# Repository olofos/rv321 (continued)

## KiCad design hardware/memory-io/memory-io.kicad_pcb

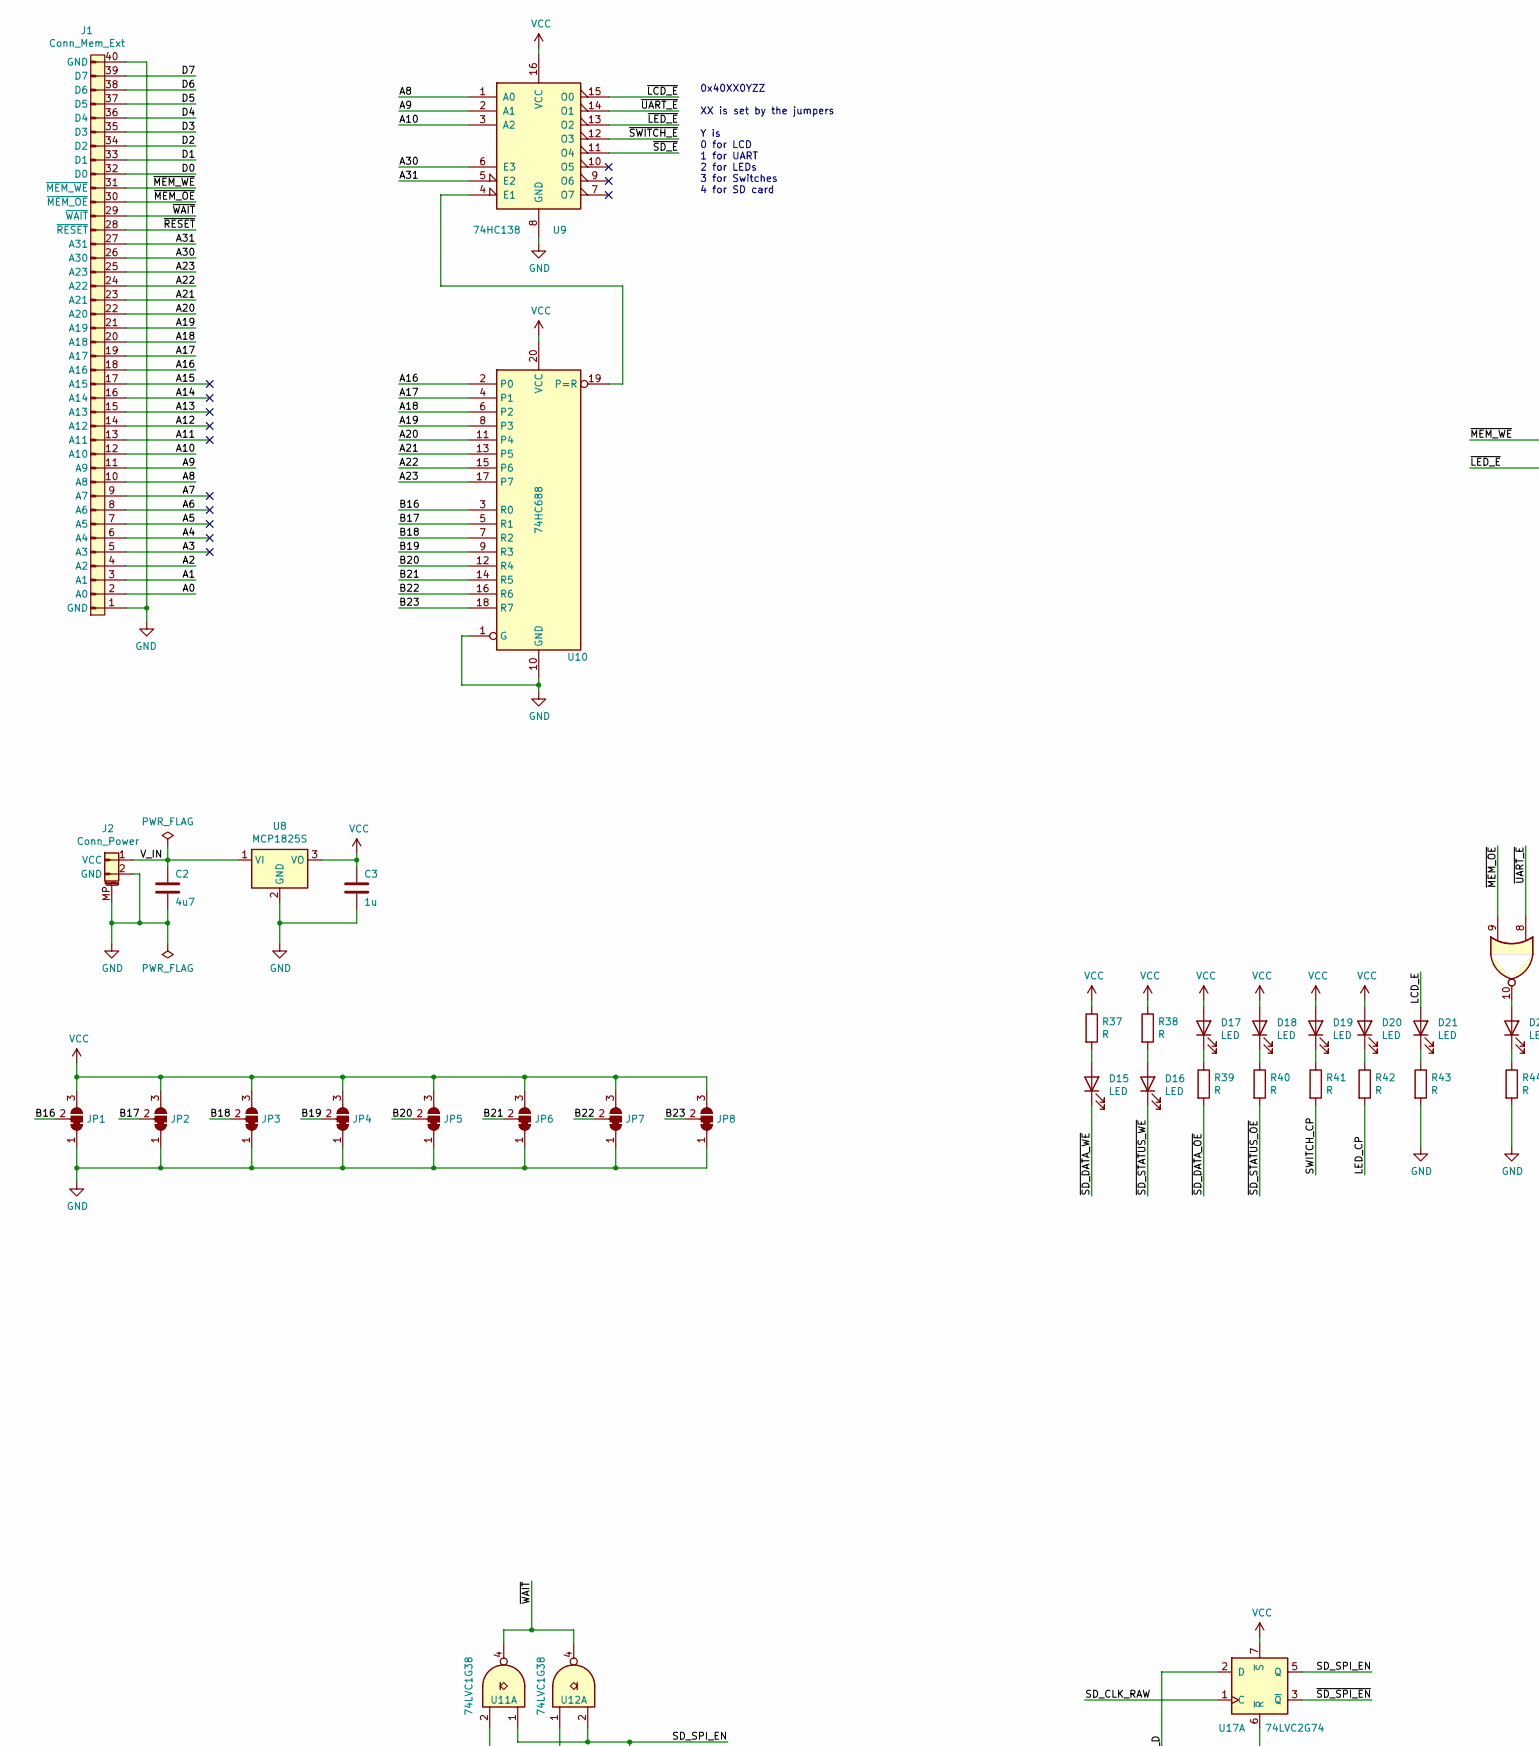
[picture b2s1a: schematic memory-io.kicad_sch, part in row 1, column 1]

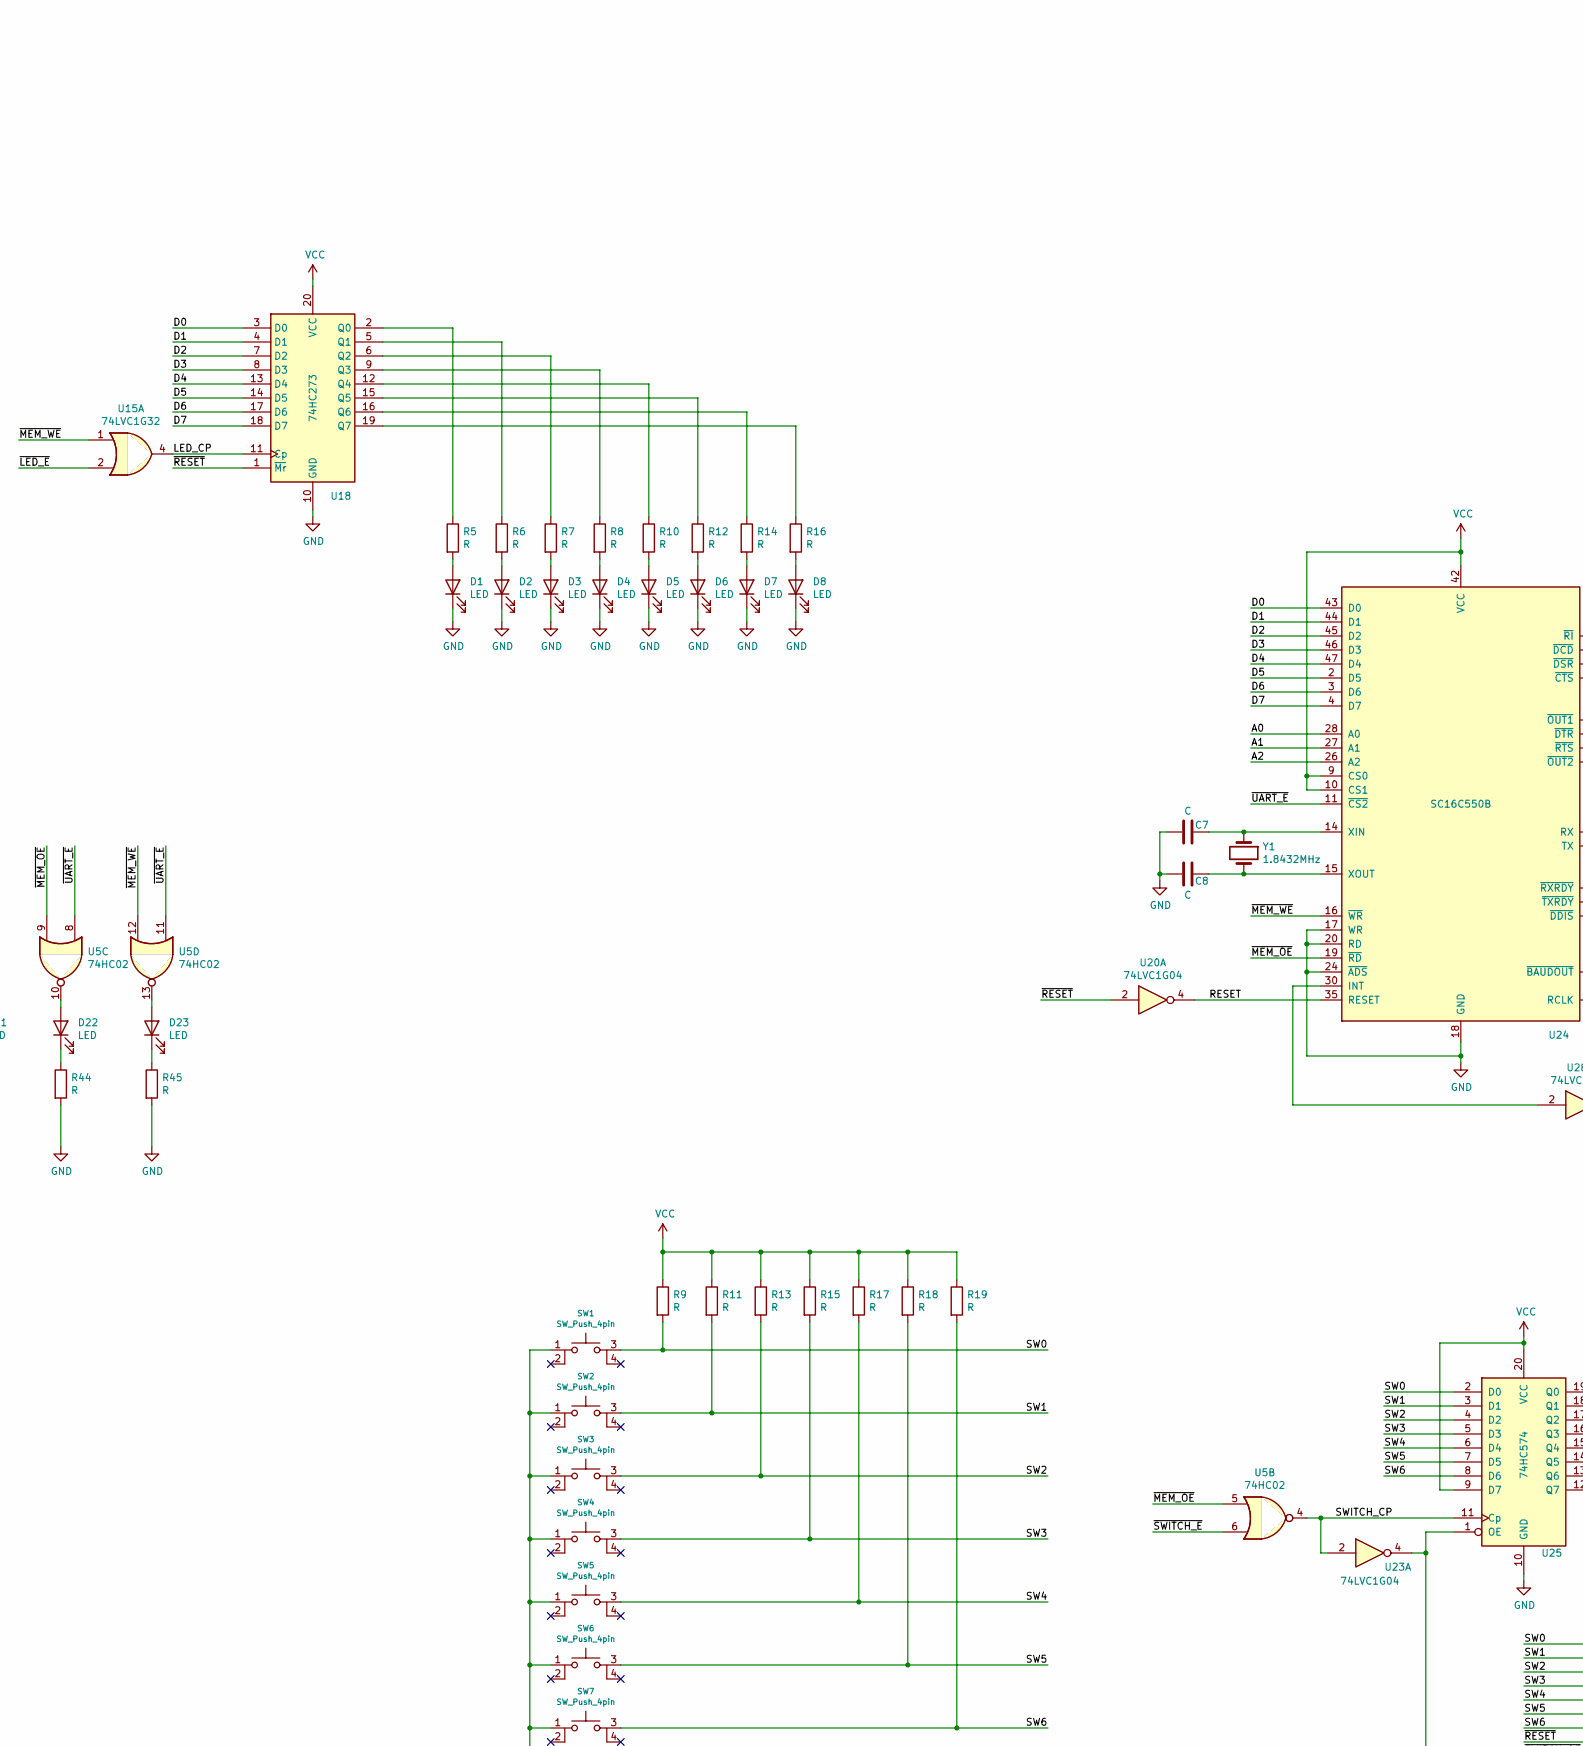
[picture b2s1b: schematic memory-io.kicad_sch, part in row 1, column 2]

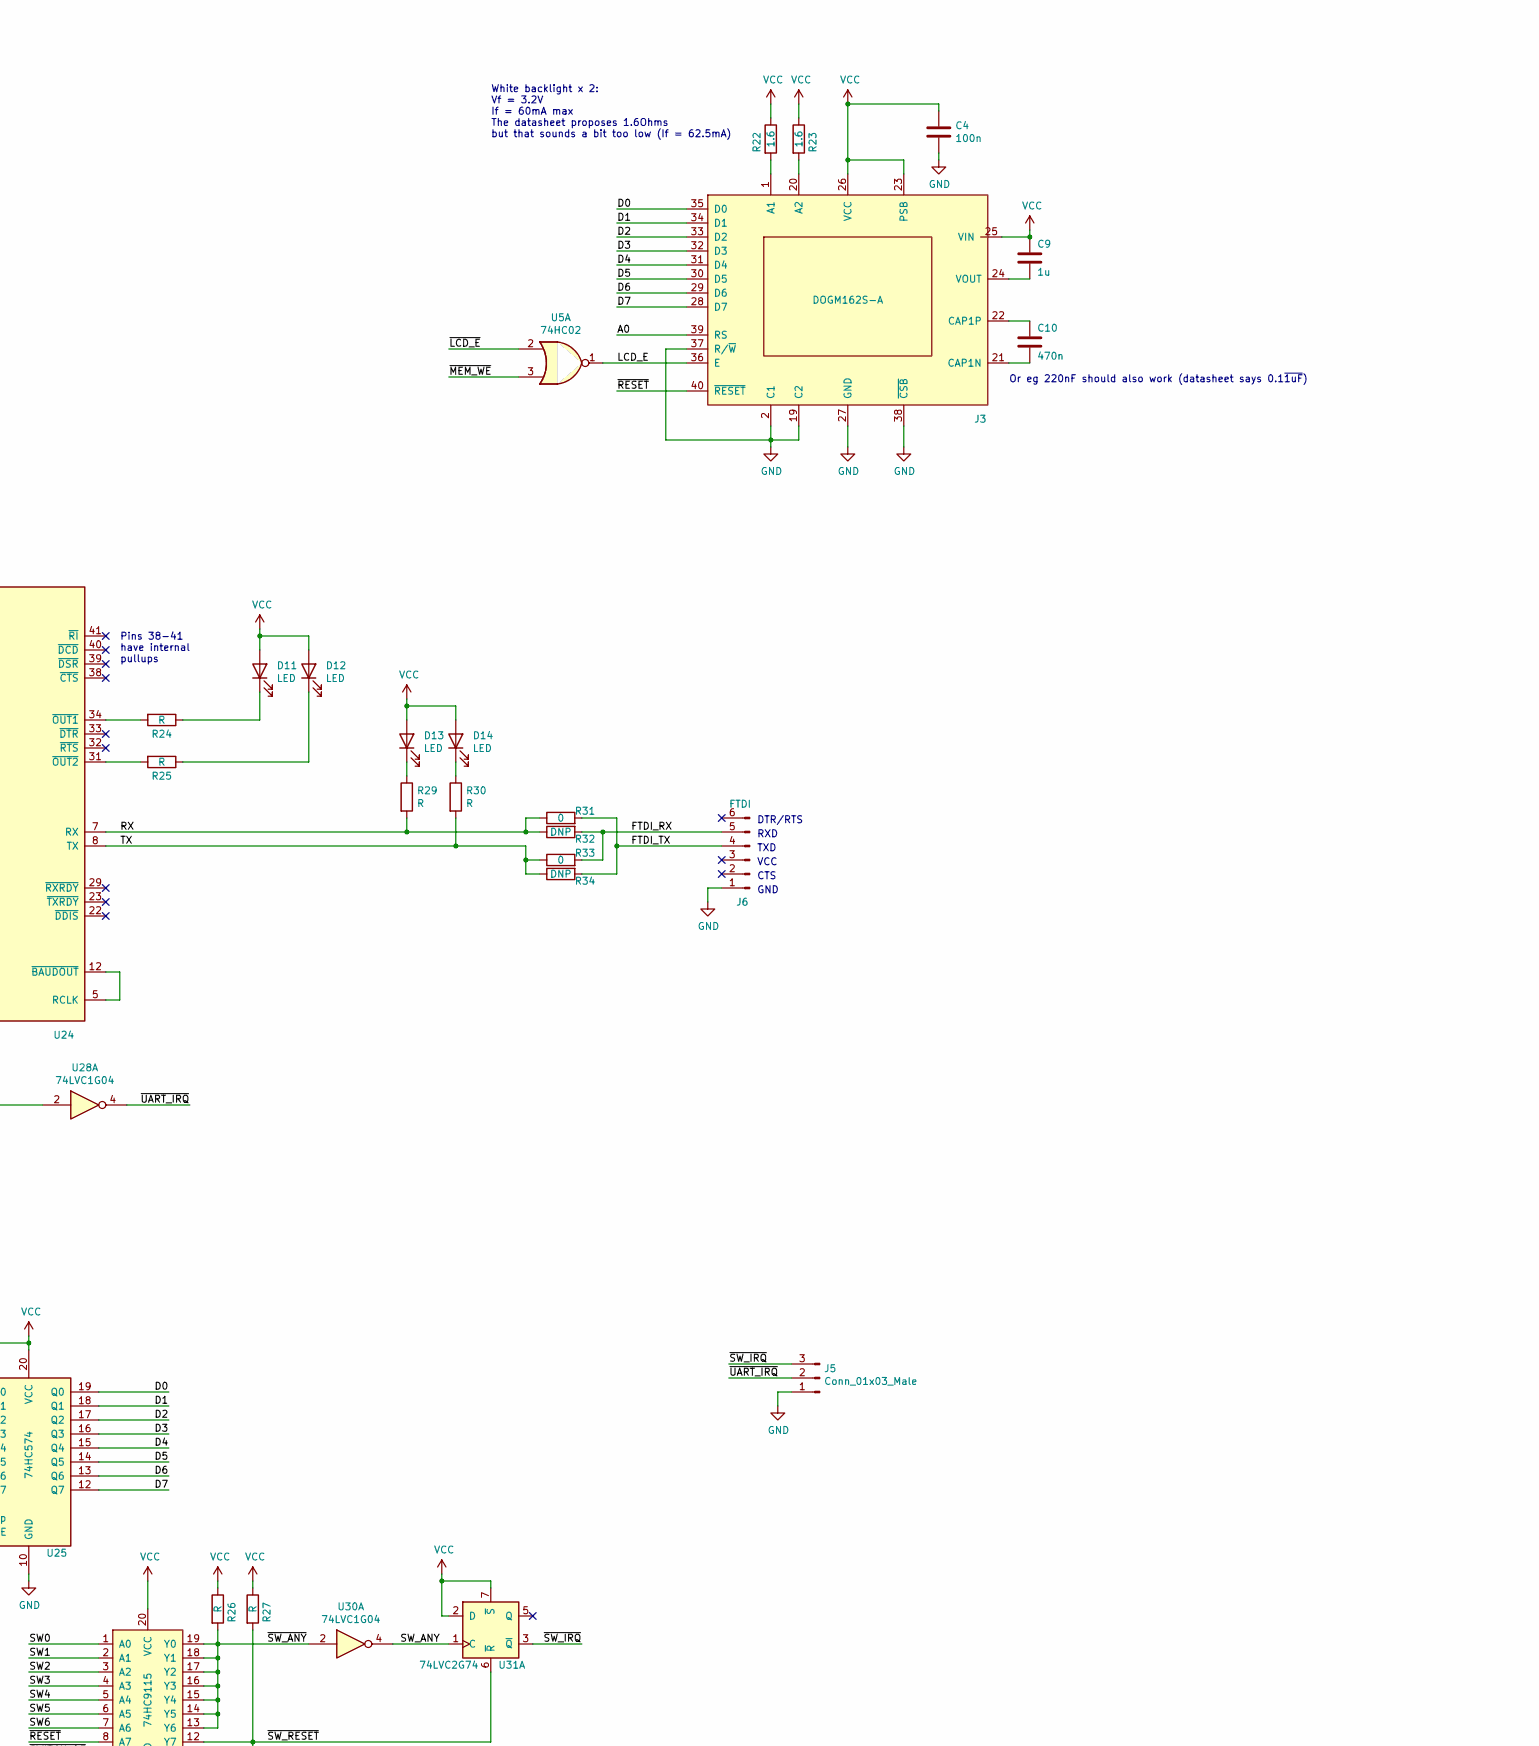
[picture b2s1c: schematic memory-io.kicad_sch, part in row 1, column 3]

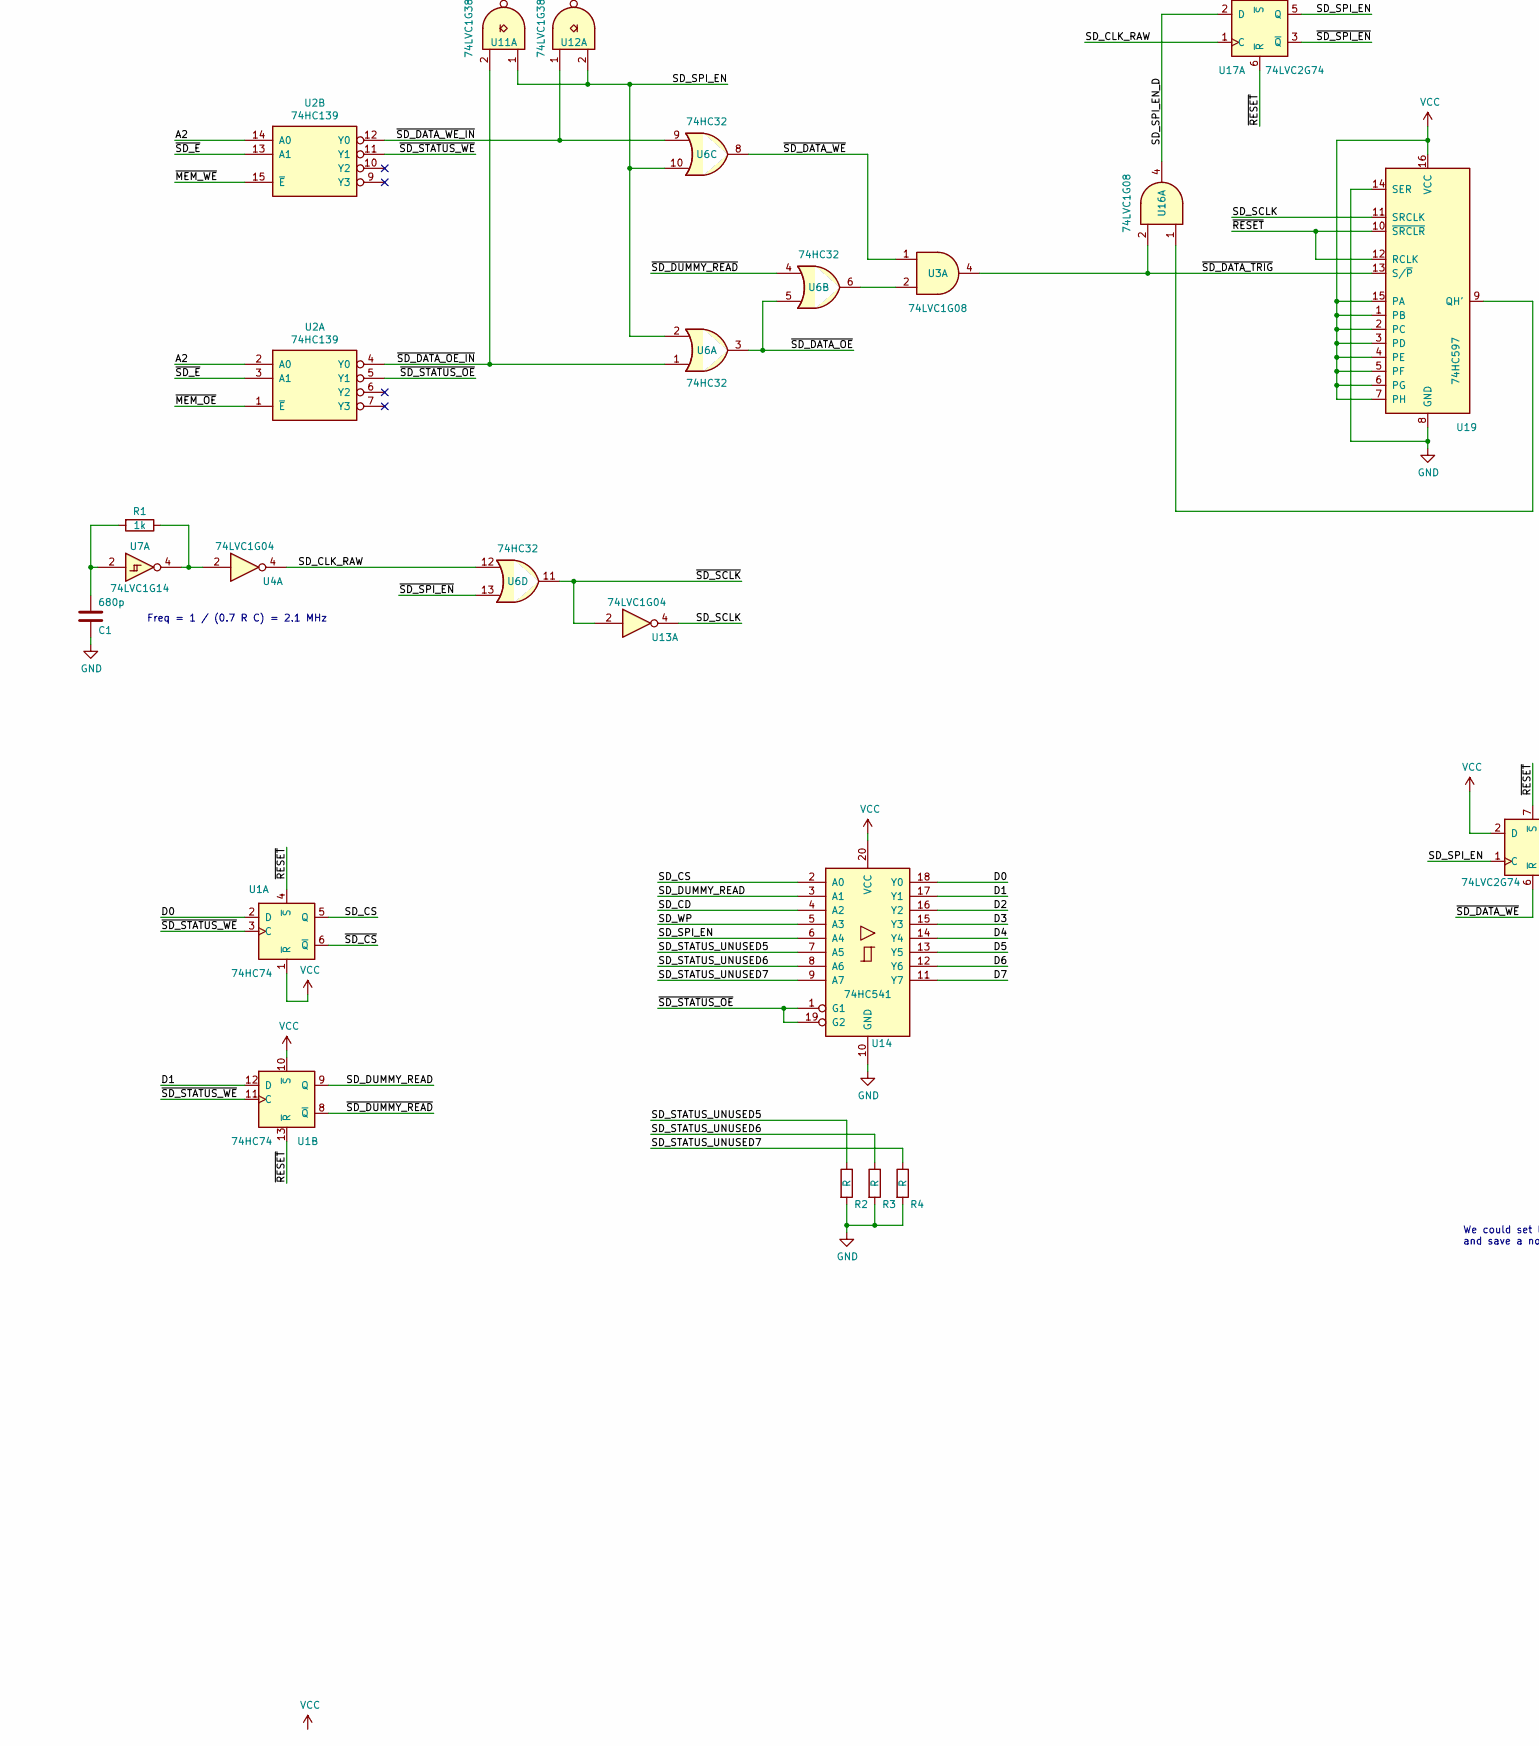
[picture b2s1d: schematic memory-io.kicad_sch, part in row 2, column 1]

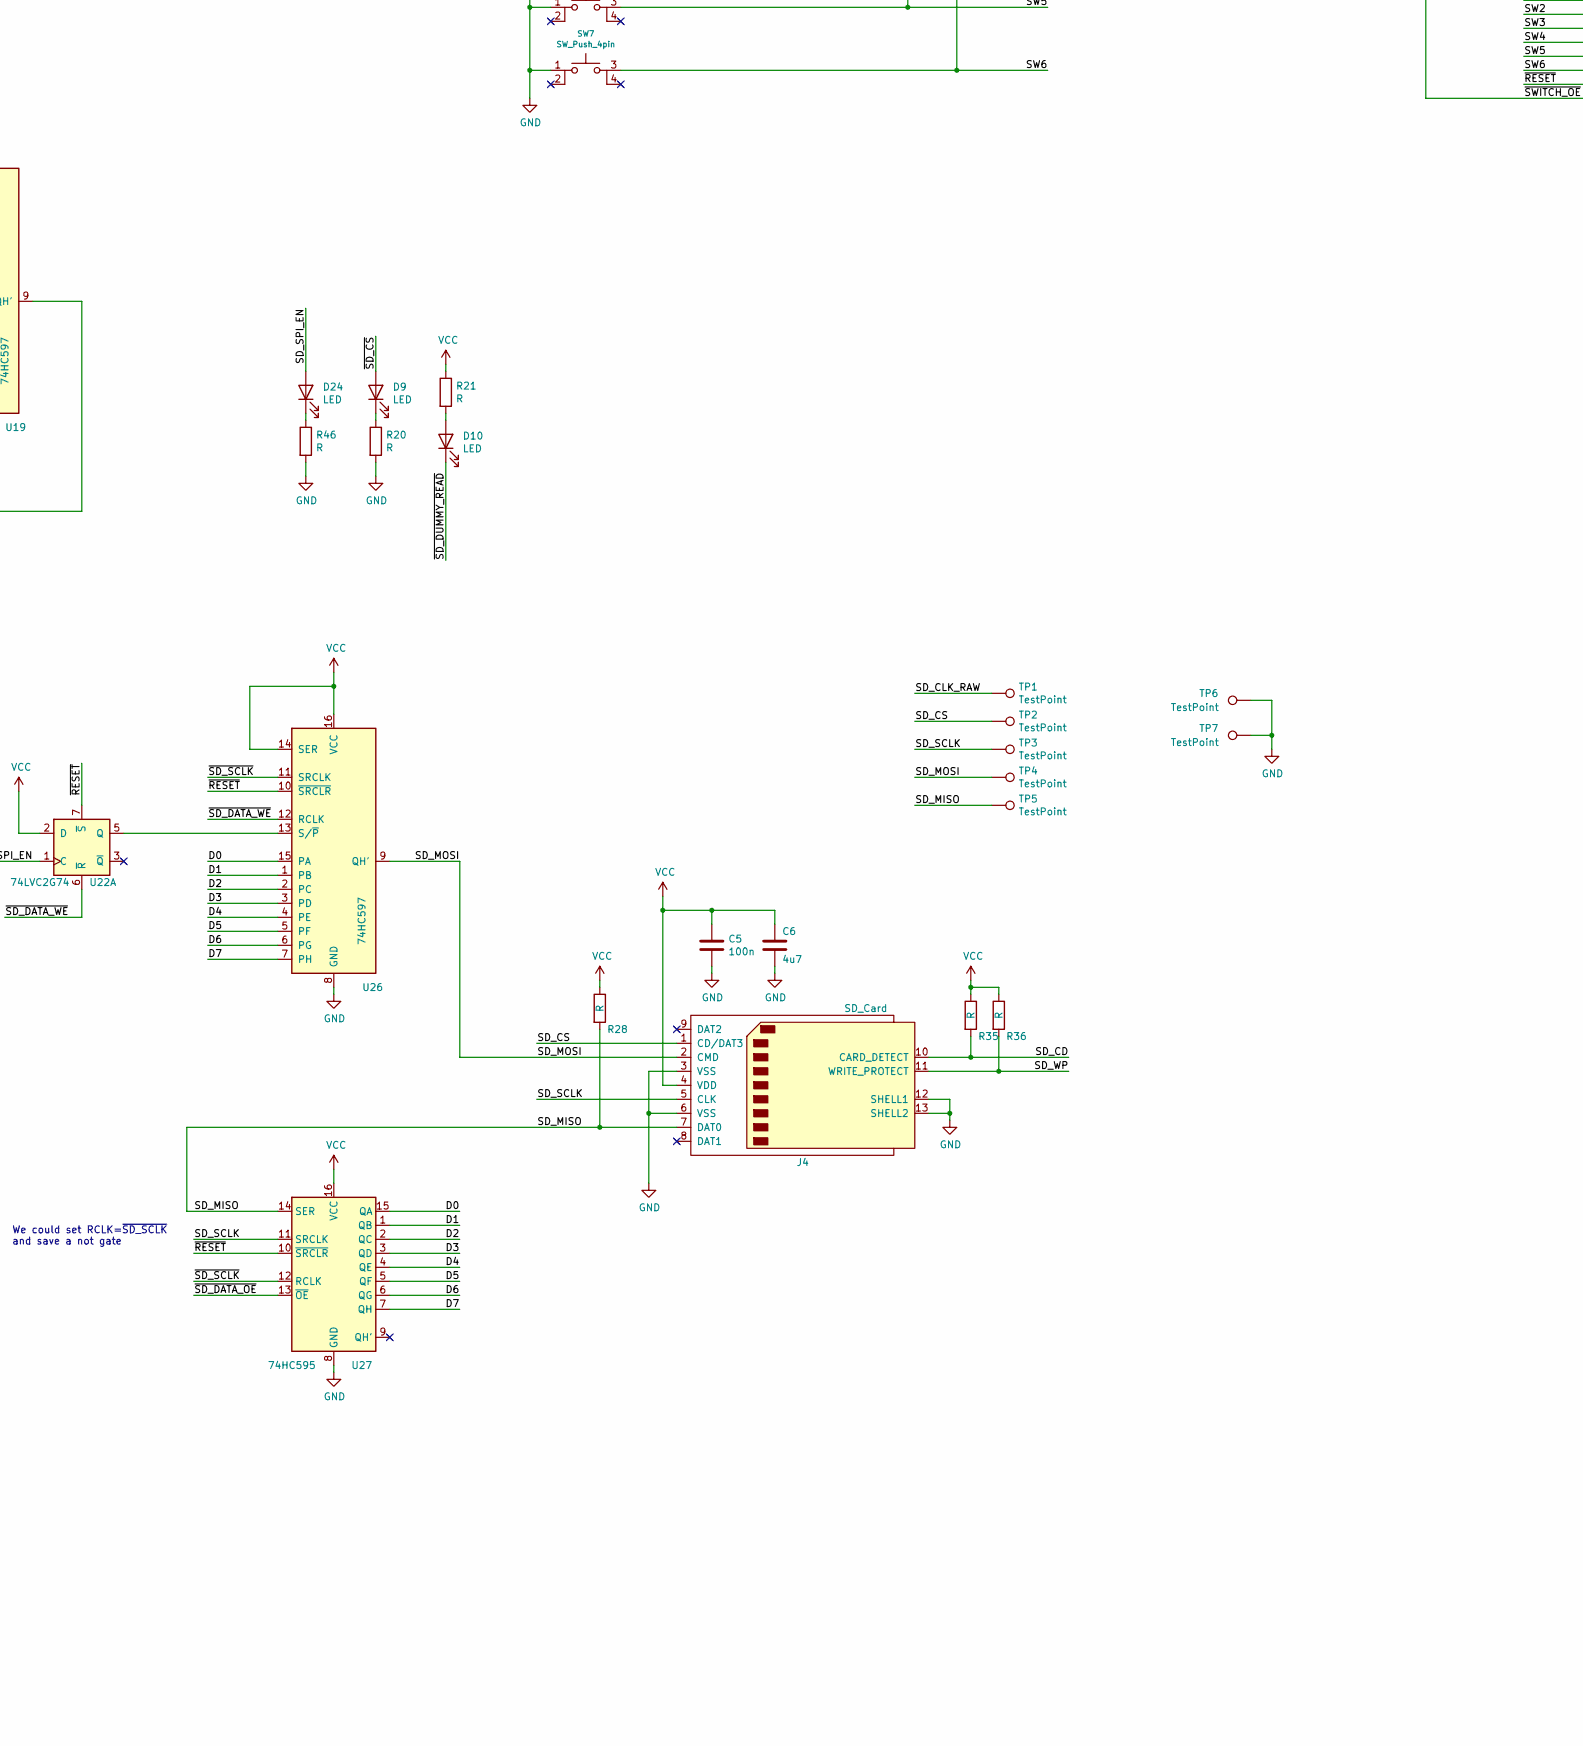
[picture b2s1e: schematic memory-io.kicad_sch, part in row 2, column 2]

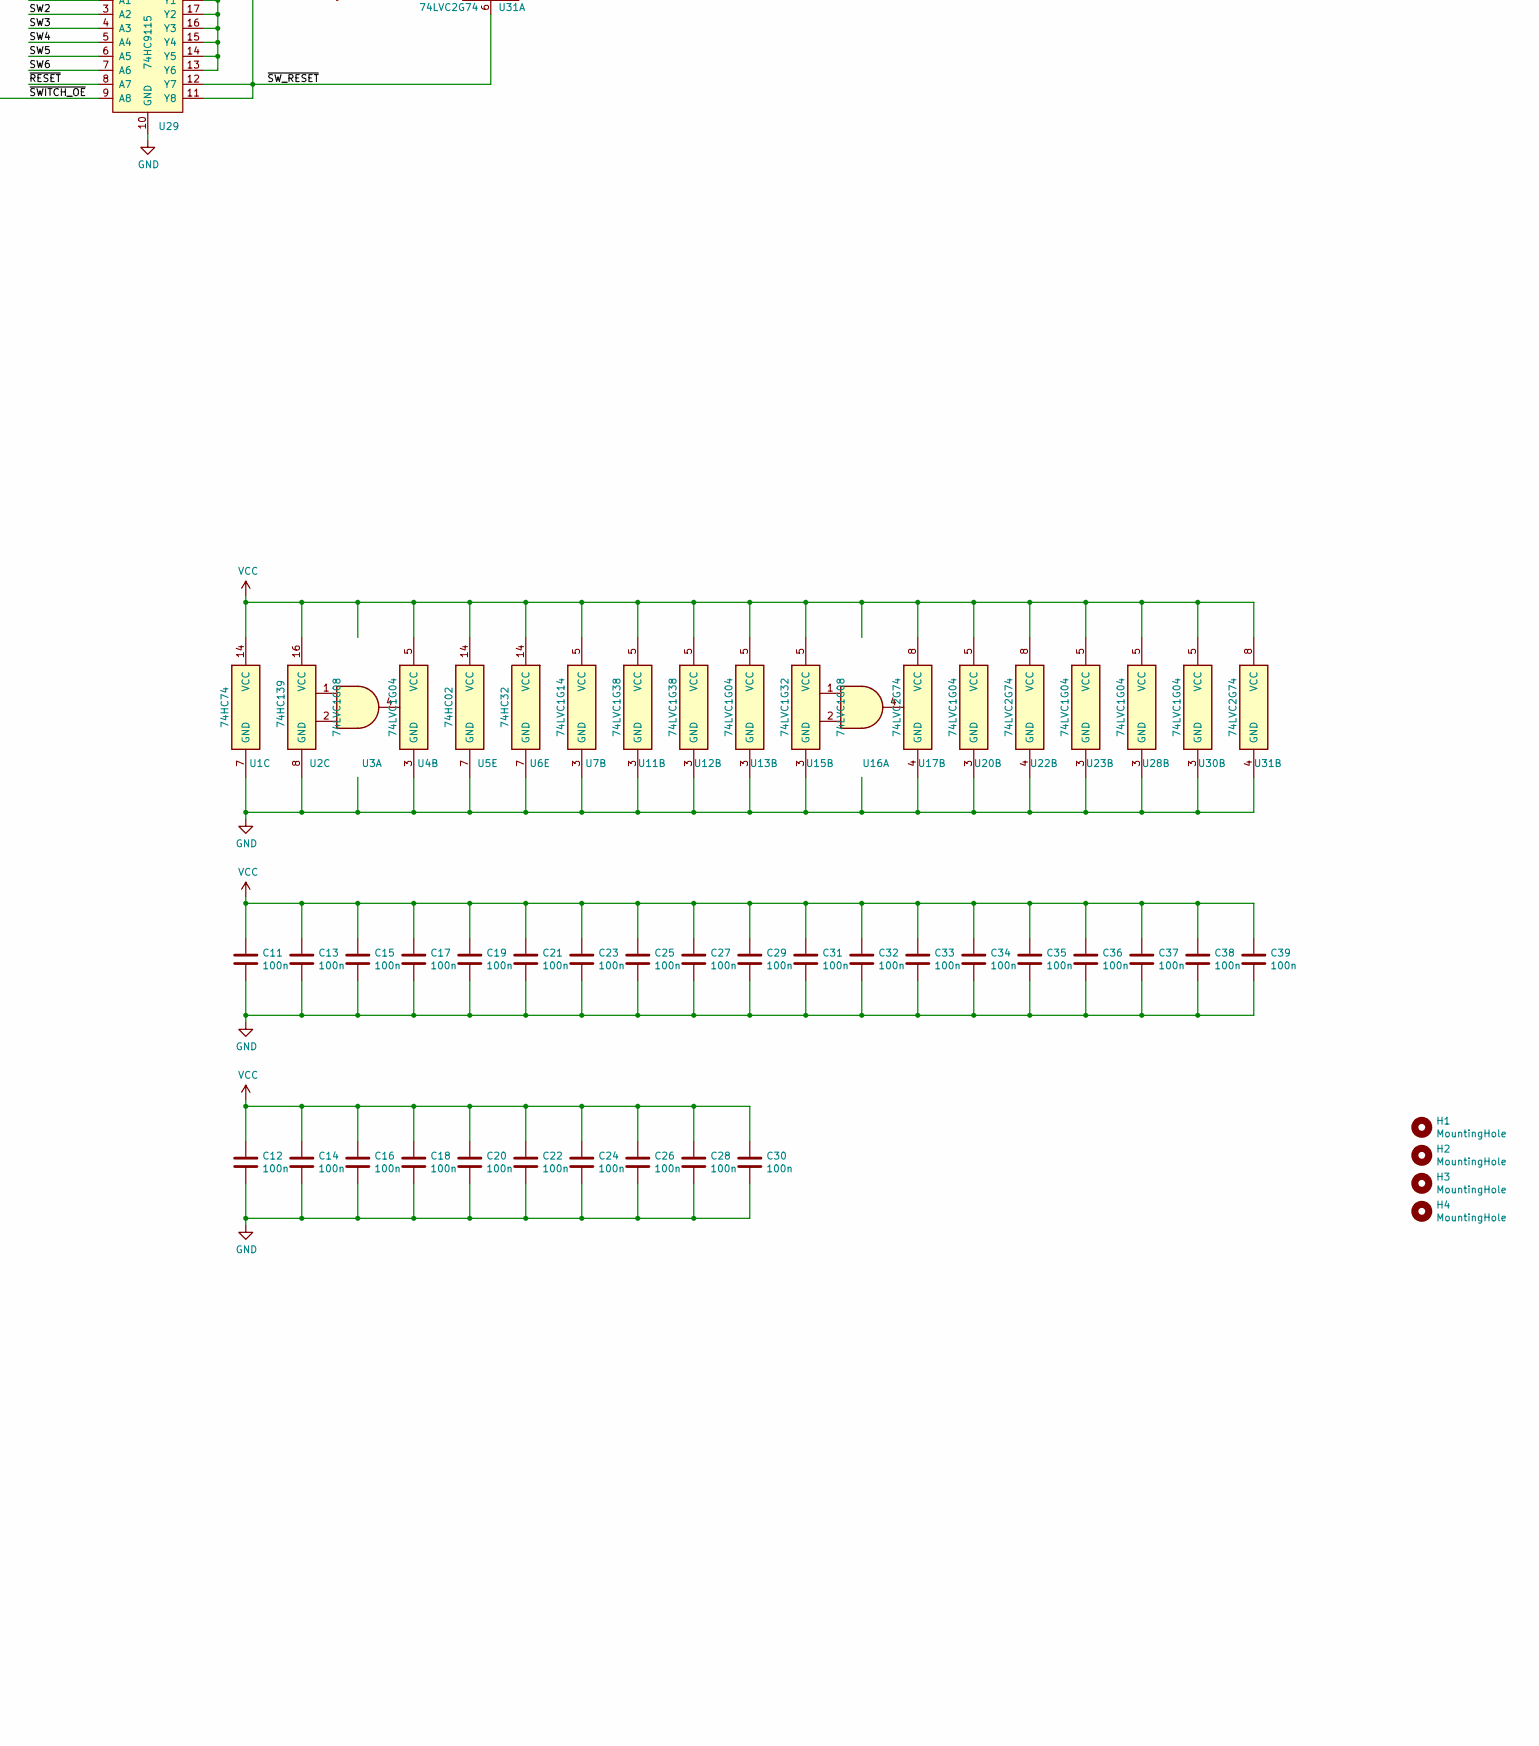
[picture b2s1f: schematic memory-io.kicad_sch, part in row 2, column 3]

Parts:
C1: 680p; C_0805_2012Metric_Pad1.18x1.45mm_HandSolder
C2, C6: 4u7; C_0805_2012Metric_Pad1.18x1.45mm_HandSolder
C3, C9: 1u; C_0805_2012Metric_Pad1.18x1.45mm_HandSolder
C4, C5, C11, C12, C13, C14, C15, C16, C17, C18, C19, C20, C21, C22, C23, C24, C25, C26, C27, C28, C29, C30, C31, C32, C33, C34, C35, C36, C37, C38, C39: 100n; C_0805_2012Metric_Pad1.18x1.45mm_HandSolder
C7, C8: C; C_0805_2012Metric_Pad1.18x1.45mm_HandSolder
C10: 470n; C_0805_2012Metric_Pad1.18x1.45mm_HandSolder
D1, D2, D3, D4, D5, D6, D7, D8, D9, D10, D11, D12, D13, D14, D15, D16, D17, D18, D19, D20, D21, D22, D23, D24: LED; LED_0805_2012Metric_Pad1.15x1.40mm_HandSolder
H1, H2, H3, H4: MountingHole; MountingHole_3.2mm_M3
J1: Conn_Mem_Ext; IDC-Header_2x20_P2.54mm_Vertical
J2: Conn_Power; JST_PH_S2B-PH-SM4-TB_1x02-1MP_P2.00mm_Horizontal
J3: DOGM162S-A; EA-DOGM
J4: SD_Card; SD_Kyocera_145638009211859+
J5: Conn_01x03_Male; PinHeader_1x03_P2.54mm_Vertical
J6: FTDI; PinHeader_1x06_P2.54mm_Vertical
JP1, JP2, JP3, JP4, JP5, JP6, JP7, JP8: SolderJumper_3_Bridged12; SolderJumper-3_P1.3mm_Bridged2Bar12_RoundedPad1.0x1.5mm
R1: 1k; R_0805_2012Metric_Pad1.20x1.40mm_HandSolder
R2, R3, R4, R5, R6, R7, R8, R9, R10, R11, R12, R13, R14, R15, R16, R17, R18, R19, R20, R21, R24, R25, R26, R27, R28, R29, R30, R35, R36, R37, R38, R39, R40, R41, R42, R43, R44, R45, R46: R; R_0805_2012Metric_Pad1.20x1.40mm_HandSolder
R22, R23: 1.6; R_1206_3216Metric_Pad1.30x1.75mm_HandSolder
R31, R33: 0; R_0805_2012Metric_Pad1.20x1.40mm_HandSolder
R32, R34: DNP; R_0805_2012Metric_Pad1.20x1.40mm_HandSolder
SW1, SW2, SW3, SW4, SW5, SW6, SW7: SW_Push_4pin; SW_SPST_DTSM-6
TP1, TP2, TP3, TP4, TP5: TestPoint; TestPoint_THTPad_D1.5mm_Drill0.7mm
TP6, TP7: TestPoint; TestPoint_THTPad_D2.0mm_Drill1.0mm
U1: 74HC74; SOIC-14_3.9x8.7mm_P1.27mm
U2: 74HC139; SOIC-16_3.9x9.9mm_P1.27mm
U3, U16: 74LVC1G08; SOT-23-5_HandSoldering
U4, U13, U20, U23, U28, U30: 74LVC1G04; SOT-23-5_HandSoldering
U5: 74HC02; SOIC-14_3.9x8.7mm_P1.27mm
U6: 74HC32; SOIC-14_3.9x8.7mm_P1.27mm
U7: 74LVC1G14; SOT-23-5_HandSoldering
U8: MCP1825S; SOT-223-3_TabPin2
U9: 74HC138; SOIC-16_3.9x9.9mm_P1.27mm
U10: 74HC688; SOIC-20W_7.5x12.8mm_P1.27mm
U11, U12: 74LVC1G38; SOT-23-5_HandSoldering
U14: 74HC541; SOIC-20W_7.5x12.8mm_P1.27mm
U15: 74LVC1G32; SOT-23-5_HandSoldering
U17, U22: 74LVC2G74; SOT-23-8_Handsoldering
U18: 74HC273; SOIC-20W_7.5x12.8mm_P1.27mm
U19, U26: 74HC597; SOIC-16_3.9x9.9mm_P1.27mm
U24: SC16C550B; LQFP-48_7x7mm_P0.5mm
U25: 74HC574; SOIC-20W_7.5x12.8mm_P1.27mm
U27: 74HC595; SOIC-16_3.9x9.9mm_P1.27mm
U29: 74HC9115; SOIC-20W_7.5x12.8mm_P1.27mm
U31: 74LVC2G74; TSSOP-8_3x3mm_P0.65mm
Y1: 1.8432MHz; Crystal_HC49-U_Vertical

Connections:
/A0: J1.2 (A0), J3.39 (RS), U24.28 (A0)
/A1: J1.3 (A1), U24.27 (A1)
/A2: J1.4 (A2), U2.2 (A0), U2.14 (A0), U24.26 (A2)
/A3: J1.5 (A3)
/A4: J1.6 (A4)
/A5: J1.7 (A5)
/A6: J1.8 (A6)
/A7: J1.9 (A7)
/A8: J1.10 (A8), U9.1 (A0)
/A9: J1.11 (A9), U9.2 (A1)
/A10: J1.12 (A10), U9.3 (A2)
/A11: J1.13 (A11)
/A12: J1.14 (A12)
/A13: J1.15 (A13)
/A14: J1.16 (A14)
/A15: J1.17 (A15)
/A16: J1.18 (A16), U10.2 (P0)
/A17: J1.19 (A17), U10.4 (P1)
/A18: J1.20 (A18), U10.6 (P2)
/A19: J1.21 (A19), U10.8 (P3)
/A20: J1.22 (A20), U10.11 (P4)
/A21: J1.23 (A21), U10.13 (P5)
/A22: J1.24 (A22), U10.15 (P6)
/A23: J1.25 (A23), U10.17 (P7)
/A30: J1.26 (A30), U9.6 (E3)
/A31: J1.27 (A31), U9.5 (E2)
/B16: JP1.2 (C), U10.3 (R0)
/B17: JP2.2 (C), U10.5 (R1)
/B18: JP3.2 (C), U10.7 (R2)
/B19: JP4.2 (C), U10.9 (R3)
/B20: JP5.2 (C), U10.12 (R4)
/B21: JP6.2 (C), U10.14 (R5)
/B22: JP7.2 (C), U10.16 (R6)
/B23: JP8.2 (C), U10.18 (R7)
/D0: J1.32 (D0), J3.35 (D0), U1.2 (D), U14.18 (Y0), U18.3 (D0), U24.43 (D0), U25.19 (Q0), U26.15 (PA), U27.15 (QA)
/D1: J1.33 (D1), J3.34 (D1), U1.12 (D), U14.17 (Y1), U18.4 (D1), U24.44 (D1), U25.18 (Q1), U26.1 (PB), U27.1 (QB)
/D2: J1.34 (D2), J3.33 (D2), U14.16 (Y2), U18.7 (D2), U24.45 (D2), U25.17 (Q2), U26.2 (PC), U27.2 (QC)
/D3: J1.35 (D3), J3.32 (D3), U14.15 (Y3), U18.8 (D3), U24.46 (D3), U25.16 (Q3), U26.3 (PD), U27.3 (QD)
/D4: J1.36 (D4), J3.31 (D4), U14.14 (Y4), U18.13 (D4), U24.47 (D4), U25.15 (Q4), U26.4 (PE), U27.4 (QE)
/D5: J1.37 (D5), J3.30 (D5), U14.13 (Y5), U18.14 (D5), U24.2 (D5), U25.14 (Q5), U26.5 (PF), U27.5 (QF)
/D6: J1.38 (D6), J3.29 (D6), U14.12 (Y6), U18.17 (D6), U24.3 (D6), U25.13 (Q6), U26.6 (PG), U27.6 (QG)
/D7: J1.39 (D7), J3.28 (D7), U14.11 (Y7), U18.18 (D7), U24.4 (D7), U25.12 (Q7), U26.7 (PH), U27.7 (QH)
/FTDI_RX: J6.5, R32.2, R33.2
/FTDI_TX: J6.4, R31.2, R34.2
/LCD_E: D21.2 (A), J3.36 (E), U5.1
/LED_CP: R42.2, U15.4, U18.11 (Cp)
/RESET: U20.4, U24.35 (RESET)
/RX: R29.2, R31.1, R32.1, U24.7 (RX)
/SD_CD: J4.10 (CARD_DETECT), R35.2, U14.4 (A2)
/SD_CLK_RAW: TP1.1, U4.4, U6.12, U17.1 (C)
/SD_CS: J4.1 (CD/DAT3), TP2.1, U1.5 (Q), U14.2 (A0)
/SD_DUMMY_READ: U1.9 (Q), U14.3 (A1)
/SD_MISO: J4.7 (DAT0), R28.2, TP5.1, U27.14 (SER)
/SD_MOSI: J4.2 (CMD), TP4.1, U26.9 (QH')
/SD_SCLK: J4.5 (CLK), TP3.1, U13.4, U19.11 (SRCLK), U27.11 (SRCLK)
/SD_SPI_EN: D24.2 (A), U6.2, U6.10, U11.1, U12.2, U14.6 (A4), U17.5 (Q), U22.1 (C)
/SD_SPI_EN_D: U16.4, U17.2 (D)
/SD_STATUS_UNUSED5: R2.1, U14.7 (A5)
/SD_STATUS_UNUSED6: R3.1, U14.8 (A6)
/SD_STATUS_UNUSED7: R4.1, U14.9 (A7)
/SD_WP: J4.11 (WRITE_PROTECT), R36.2, U14.5 (A3)
/SW0: R9.2, SW1.3, U25.2 (D0), U29.1 (A0)
/SW1: R11.2, SW2.3, U25.3 (D1), U29.2 (A1)
/SW2: R13.2, SW3.3, U25.4 (D2), U29.3 (A2)
/SW3: R15.2, SW4.3, U25.5 (D3), U29.4 (A3)
/SW4: R17.2, SW5.3, U25.6 (D4), U29.5 (A4)
/SW5: R18.2, SW6.3, U25.7 (D5), U29.6 (A5)
/SW6: R19.2, SW7.3, U25.8 (D6), U29.7 (A6)
/SWITCH_CP: R41.2, U5.4, U23.2, U25.11 (Cp)
/SW_ANY: U30.4, U31.1 (C)
/TX: R30.2, R33.1, R34.1, U24.8 (TX)
/V_IN: C2.2, J2.1 (VCC), U8.1 (VI)
/~LCD_E: U5.2, U9.15 (O0)
/~LED_E: U9.13 (O2), U15.2
/~MEM_OE: J1.30 (~MEM_OE), U2.1 (~E), U5.5, U5.9, U24.19 (~RD)
/~MEM_WE: J1.31 (~MEM_WE), U2.15 (~E), U5.3, U5.12, U15.1, U24.16 (~WR)
/~RESET: J1.28 (~RESET), J3.40 (~RESET), U1.4 (~S), U1.13 (~R), U17.6 (~R), U18.1 (~Mr), U19.10 (~SRCLR), U19.12 (RCLK), U20.2, U22.7 (~S), U26.10 (~SRCLR), U27.10 (~SRCLR), U29.8 (A7)
/~SD_CS: D9.2 (A), U1.6 (~Q)
/~SD_DATA_OE_IN: U2.4 (Y0), U6.1, U11.2
/~SD_DATA_OE: R39.2, U6.3, U6.5, U27.13 (~OE)
/~SD_DATA_TRIG: U3.4, U16.2, U19.13 (S/~P)
/~SD_DATA_WE_IN: U2.12 (Y0), U6.9, U12.1
/~SD_DATA_WE: D15.1 (K), U3.1, U6.8, U22.6 (~R), U26.12 (RCLK)
/~SD_DUMMY_READ: D10.1 (K), U1.8 (~Q), U6.4
/~SD_E: U2.3 (A1), U2.13 (A1), U9.11 (O4)
/~SD_SCLK: U6.11, U13.2, U26.11 (SRCLK), U27.12 (RCLK)
/~SD_SPI_EN: U6.13, U17.3 (~Q)
/~SD_STATUS_OE: R40.2, U2.5 (Y1), U14.1 (G1), U14.19 (G2)
/~SD_STATUS_WE: D16.1 (K), U1.3 (C), U1.11 (C), U2.11 (Y1)
/~SWITCH_E: U5.6, U9.12 (O3)
/~SWITCH_OE: U23.4, U25.1 (OE), U29.9 (A8)
/~SW_ANY: R26.2, U29.13 (Y6), U29.14 (Y5), U29.15 (Y4), U29.16 (Y3), U29.17 (Y2), U29.18 (Y1), U29.19 (Y0), U30.2
/~SW_IRQ: J5.3, U31.3 (~Q)
/~SW_RESET: R27.2, U29.11 (Y8), U29.12 (Y7), U31.6 (~R)
/~UART_E: U5.8, U5.11, U9.14 (O1), U24.11 (~CS2)
/~UART_IRQ: J5.2, U28.4
/~WAIT: J1.29 (~WAIT), U11.4, U12.4
GND: C1.2, C2.1, C3.1, C4.2, C5.2, C6.1, C7.2, C8.2, C11.2, C12.2, C13.2, C14.2, C15.2, C16.2, C17.2, C18.2, C19.2, C20.2, C21.2, C22.2, C23.2, C24.2, C25.2, C26.2, C27.2, C28.2, C29.2, C30.2, C31.2, C32.2, C33.2, C34.2, C35.2, C36.2, C37.2, C38.2, C39.2, D1.1 (K), D2.1 (K), D3.1 (K), D4.1 (K), D5.1 (K), D6.1 (K), D7.1 (K), D8.1 (K), J1.1 (GND), J1.40 (GND), J2.2 (GND), J2.MP, J3.2 (C1), J3.19 (C2), J3.27 (GND), J3.37 (R/~W), J3.38 (~CSB), J4.3 (VSS), J4.6 (VSS), J4.12 (SHELL1), J4.13 (SHELL2), J5.1, J6.1, JP1.1 (A), JP2.1 (A), JP3.1 (A), JP4.1 (A), JP5.1 (A), JP6.1 (A), JP7.1 (A), JP8.1 (A), R2.2, R3.2, R4.2, R20.2, R43.2, R44.2, R45.2, R46.2, SW1.1, SW2.1, SW3.1, SW4.1, SW5.1, SW6.1, SW7.1, TP6.1, TP7.1, U1.7 (GND), U2.8 (GND), U3.3 (GND), U4.3 (GND), U5.7 (GND), U6.7 (GND), U7.3 (GND), U8.2 (GND), U9.8 (GND), U10.1 (G), U10.10 (GND), U11.3 (GND), U12.3 (GND), U13.3 (GND), U14.10 (GND), U15.3 (GND), U16.3 (GND), U17.4 (GND), U18.10 (GND), U19.8 (GND), U19.14 (SER), U20.3 (GND), U22.4 (GND), U23.3 (GND), U24.17 (WR), U24.18 (GND), U24.20 (RD), U24.24 (~ADS), U25.10 (GND), U26.8 (GND), U27.8 (GND), U28.3 (GND), U29.10 (GND), U30.3 (GND), U31.4 (GND)
unnamed: C1.1, R1.2, U7.2
unnamed: C7.1, U24.14 (XIN), Y1.1
unnamed: C8.1, U24.15 (XOUT), Y1.2
unnamed: C9.1, J3.24 (VOUT)
unnamed: C10.1, J3.21 (CAP1N)
unnamed: C10.2, J3.22 (CAP1P)
unnamed: D1.2 (A), R5.2
unnamed: D2.2 (A), R6.2
unnamed: D3.2 (A), R7.2
unnamed: D4.2 (A), R8.2
unnamed: D5.2 (A), R10.2
unnamed: D6.2 (A), R12.2
unnamed: D7.2 (A), R14.2
unnamed: D8.2 (A), R16.2
unnamed: D9.1 (K), R20.1
unnamed: D10.2 (A), R21.2
unnamed: D11.1 (K), R24.1
unnamed: D12.1 (K), R25.1
unnamed: D13.1 (K), R29.1
unnamed: D14.1 (K), R30.1
unnamed: D15.2 (A), R37.2
unnamed: D16.2 (A), R38.2
unnamed: D17.1 (K), R39.1
unnamed: D18.1 (K), R40.1
unnamed: D19.1 (K), R41.1
unnamed: D20.1 (K), R42.1
unnamed: D21.1 (K), R43.1
unnamed: D22.1 (K), R44.1
unnamed: D22.2 (A), U5.10
unnamed: D23.1 (K), R45.1
unnamed: D23.2 (A), U5.13
unnamed: D24.1 (K), R46.1
unnamed: J3.1 (A1), R22.2
unnamed: J3.20 (A2), R23.2
unnamed: R1.1, U4.2, U7.4
unnamed: R5.1, U18.2 (Q0)
unnamed: R6.1, U18.5 (Q1)
unnamed: R7.1, U18.6 (Q2)
unnamed: R8.1, U18.9 (Q3)
unnamed: R10.1, U18.12 (Q4)
unnamed: R12.1, U18.15 (Q5)
unnamed: R14.1, U18.16 (Q6)
unnamed: R16.1, U18.19 (Q7)
unnamed: R24.2, U24.34 (~OUT1)
unnamed: R25.2, U24.31 (~OUT2)
unnamed: U3.2, U6.6
unnamed: U9.4 (E1), U10.19 (P=R)
unnamed: U16.1, U19.9 (QH')
unnamed: U22.5 (Q), U26.13 (S/~P)
unnamed: U24.5 (RCLK), U24.12 (~BAUDOUT)
unnamed: U24.30 (INT), U28.2
VCC: C3.2, C4.1, C5.1, C6.2, C9.2, C11.1, C12.1, C13.1, C14.1, C15.1, C16.1, C17.1, C18.1, C19.1, C20.1, C21.1, C22.1, C23.1, C24.1, C25.1, C26.1, C27.1, C28.1, C29.1, C30.1, C31.1, C32.1, C33.1, C34.1, C35.1, C36.1, C37.1, C38.1, C39.1, D11.2 (A), D12.2 (A), D13.2 (A), D14.2 (A), D17.2 (A), D18.2 (A), D19.2 (A), D20.2 (A), J3.23 (PSB), J3.25 (VIN), J3.26 (VCC), J4.4 (VDD), JP1.3 (B), JP2.3 (B), JP3.3 (B), JP4.3 (B), JP5.3 (B), JP6.3 (B), JP7.3 (B), JP8.3 (B), R9.1, R11.1, R13.1, R15.1, R17.1, R18.1, R19.1, R21.1, R22.1, R23.1, R26.1, R27.1, R28.1, R35.1, R36.1, R37.1, R38.1, U1.1 (~R), U1.10 (~S), U1.14 (VCC), U2.16 (VCC), U3.5 (VCC), U4.5 (VCC), U5.14 (VCC), U6.14 (VCC), U7.5 (VCC), U8.3 (VO), U9.16 (VCC), U10.20 (VCC), U11.5 (VCC), U12.5 (VCC), U13.5 (VCC), U14.20 (VCC), U15.5 (VCC), U16.5 (VCC), U17.7 (~S), U17.8 (VCC), U18.20 (VCC), U19.1 (PB), U19.2 (PC), U19.3 (PD), U19.4 (PE), U19.5 (PF), U19.6 (PG), U19.7 (PH), U19.15 (PA), U19.16 (VCC), U20.5 (VCC), U22.2 (D), U22.8 (VCC), U23.5 (VCC), U24.9 (CS0), U24.10 (CS1), U24.42 (VCC), U25.9 (D7), U25.20 (VCC), U26.14 (SER), U26.16 (VCC), U27.16 (VCC), U28.5 (VCC), U29.20 (VCC), U30.5 (VCC), U31.2 (D), U31.7 (~S), U31.8 (VCC)

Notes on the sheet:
TXD
CTS
Pins 38-41 have internal pullups
GND
White backlight x 2: Vf = 3.2V If = 60mA max The datasheet proposes 1.6Ohms but that sounds a bit too low (If = 62.5mA)
RXD
We could set RCLK=~{SD_SCLK} and save a not gate
DTR/RTS
0x40XX0YZZ XX is set by the jumpers Y is 0 for LCD 1 for UART 2 for LEDs 3 for Switches 4 for SD card
Freq = 1 / (0.7 R C) = 2.1 MHz
VCC
Or eg 220nF should also work (datasheet says 0.1~{1uF})
